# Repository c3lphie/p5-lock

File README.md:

# p5-lock

This repository contains eagle projects and libraries used in the p5 examproject

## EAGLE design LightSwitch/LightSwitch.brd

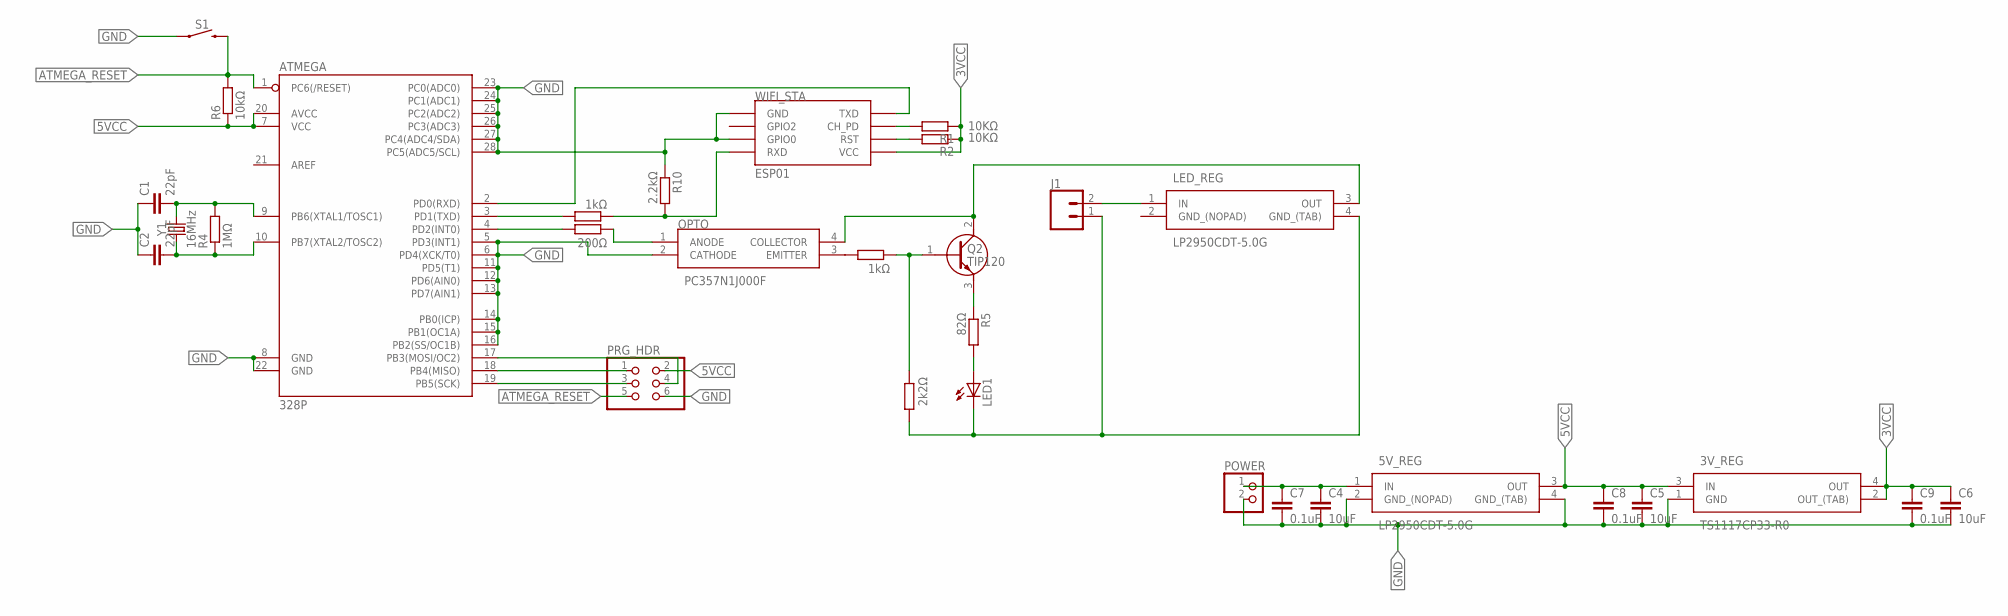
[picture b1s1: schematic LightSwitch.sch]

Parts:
3V_REG: TS1117CP33-R0; TO229P990X238-4N
5V_REG: LP2950CDT-5.0G; TO229P990X238-4N
ATMEGA: 328P; DIP28
C1, C2: 22pF; 1206
C4, C5, C6: 10uF; 1206
C7, C8, C9: 0.1uF; 1206
J1: CONN_025MM; SCREWTERMINAL-5MM-2
LED1: LED_ELD260; LED_LD260
LED_REG: LP2950CDT-5.0G; TO229P990X238-4N
OPTO: PC357N1J000F; SOP254P675X300-4N
POWER: PINHD-1X2; 1X02
PRG_HDR: PINHD-2X3; 2X03
Q2: TIP120; TO220
R1, R2: 10KΩ; R1210
R3: 200Ω; R1210
R4: 1MΩ; R1210
R5: 82Ω; R1210
R6: 10kΩ; R1210
R7, R9: 1kΩ; R1210
R8: 2k2Ω; R1210
R10: 2.2kΩ; R1210
S1: MOMENTARY-SWITCH-SPST-PTH-6.0MM; TACTILE_SWITCH_PTH_6.0MM
WIFI_STA: ESP01
Y1: 16MHz; HC49UP

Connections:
3VCC: 3V_REG.2 (OUT_(TAB)), 3V_REG.4 (OUT), C6.1, C9.1, R1.1, R2.1, WIFI_STA.VCC
5VCC: 3V_REG.3 (IN), 5V_REG.3 (OUT), ATMEGA.7 (VCC), ATMEGA.20 (AVCC), C5.1, C8.1, PRG_HDR.2, R6.1
ATMEGA_RESET: ATMEGA.1 (PC6(/RESET)), PRG_HDR.5, R6.2, S1.3 (2)
AT_TXD: ATMEGA.3 (PD1(TXD)), R9.2
GND: 3V_REG.1 (GND), 5V_REG.2 (GND_(NOPAD)), 5V_REG.4 (GND_(TAB)), ATMEGA.5 (PD3(INT1)), ATMEGA.6 (PD4(XCK/T0)), ATMEGA.8 (GND), ATMEGA.11 (PD5(T1)), ATMEGA.12 (PD6(AIN0)), ATMEGA.13 (PD7(AIN1)), ATMEGA.14 (PB0(ICP)), ATMEGA.15 (PB1(OC1A)), ATMEGA.16 (PB2(SS/OC1B)), ATMEGA.22 (GND), ATMEGA.23 (PC0(ADC0)), ATMEGA.24 (PC1(ADC1)), ATMEGA.25 (PC2(ADC2)), ATMEGA.26 (PC3(ADC3)), ATMEGA.27 (PC4(ADC4/SDA)), ATMEGA.28 (PC5(ADC5/SCL)), C1.1, C2.1, C4.2, C5.2, C6.2, C7.2, C8.2, C9.2, OPTO.2 (CATHODE), POWER.2, PRG_HDR.6, R10.1, S1.1, WIFI_STA.GND, WIFI_STA.GPIO0
GND_(NOPAD): LED_REG.2 (GND_(NOPAD))
LED_ANODE: LED1.A, R5.2
LED_EN: ATMEGA.4 (PD2(INT0)), R3.2
LED_GND: J1.1, LED1.K (C), LED_REG.4 (GND_(TAB)), R8.2
LED_VCC: LED_REG.3 (OUT), OPTO.4 (COLLECTOR), Q2.2 (C)
LED_VIN: J1.2, LED_REG.1 (IN)
MISO: ATMEGA.18 (PB4(MISO)), PRG_HDR.1
MOSI: ATMEGA.17 (PB3(MOSI/OC2)), PRG_HDR.4
unnamed: OPTO.3 (EMITTER), R7.2
unnamed: Q2.3 (E), R5.1
OPTO_ANODE: OPTO.1 (ANODE), R3.1
OPTO_EMITTER: Q2.1 (B), R7.1, R8.1
SCK: ATMEGA.19 (PB5(SCK)), PRG_HDR.3
STA_CH_PD: R1.2, WIFI_STA.CH_PD
STA_RST: R2.2, WIFI_STA.RST
STA_RXD: R9.1, R10.2, WIFI_STA.RX (RXD)
STA_TXD: ATMEGA.2 (PD0(RXD)), WIFI_STA.TX (TXD)
VIN: 5V_REG.1 (IN), C4.1, C7.1, POWER.1
XTAL1: ATMEGA.9 (PB6(XTAL1/TOSC1)), C1.2, R4.2, Y1.2
XTAL2: ATMEGA.10 (PB7(XTAL2/TOSC2)), C2.2, R4.1, Y1.1

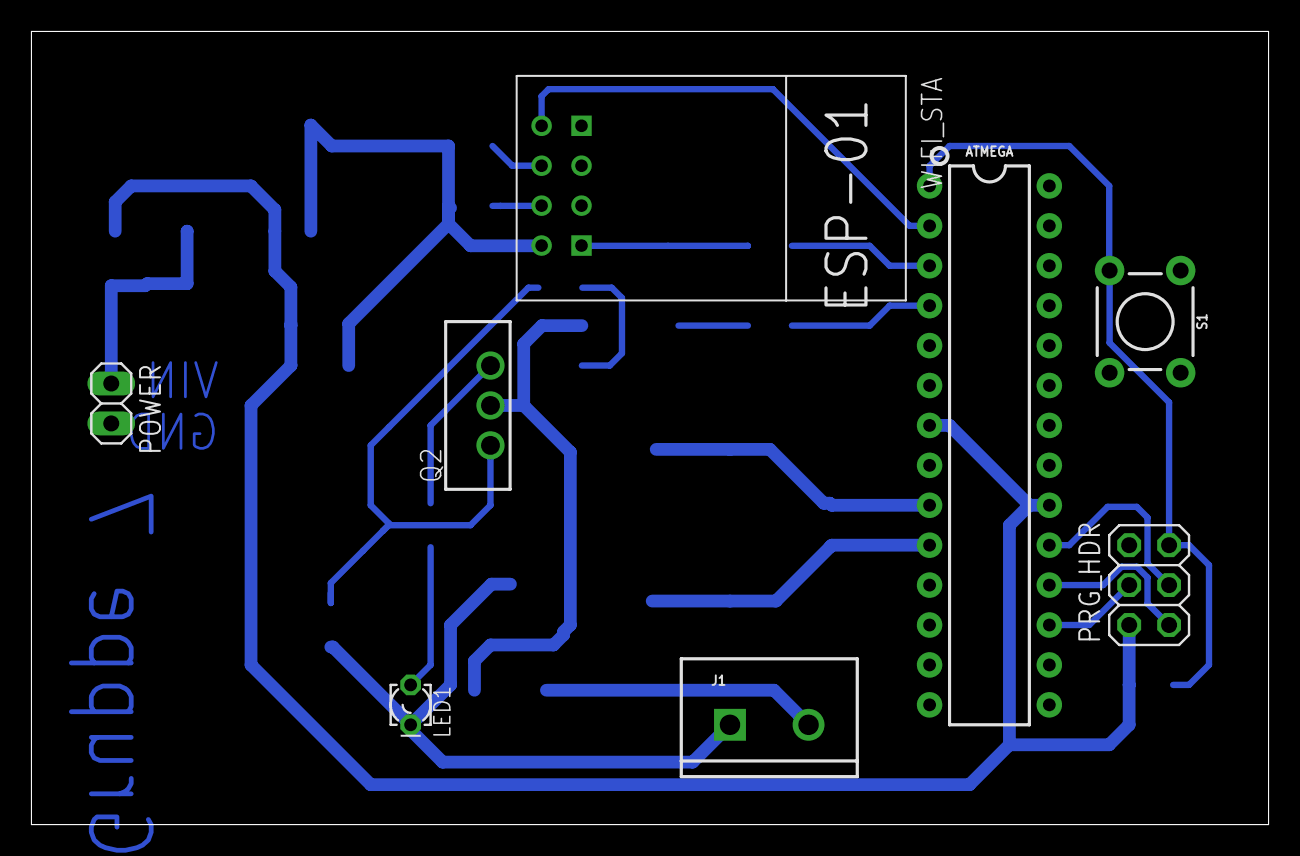
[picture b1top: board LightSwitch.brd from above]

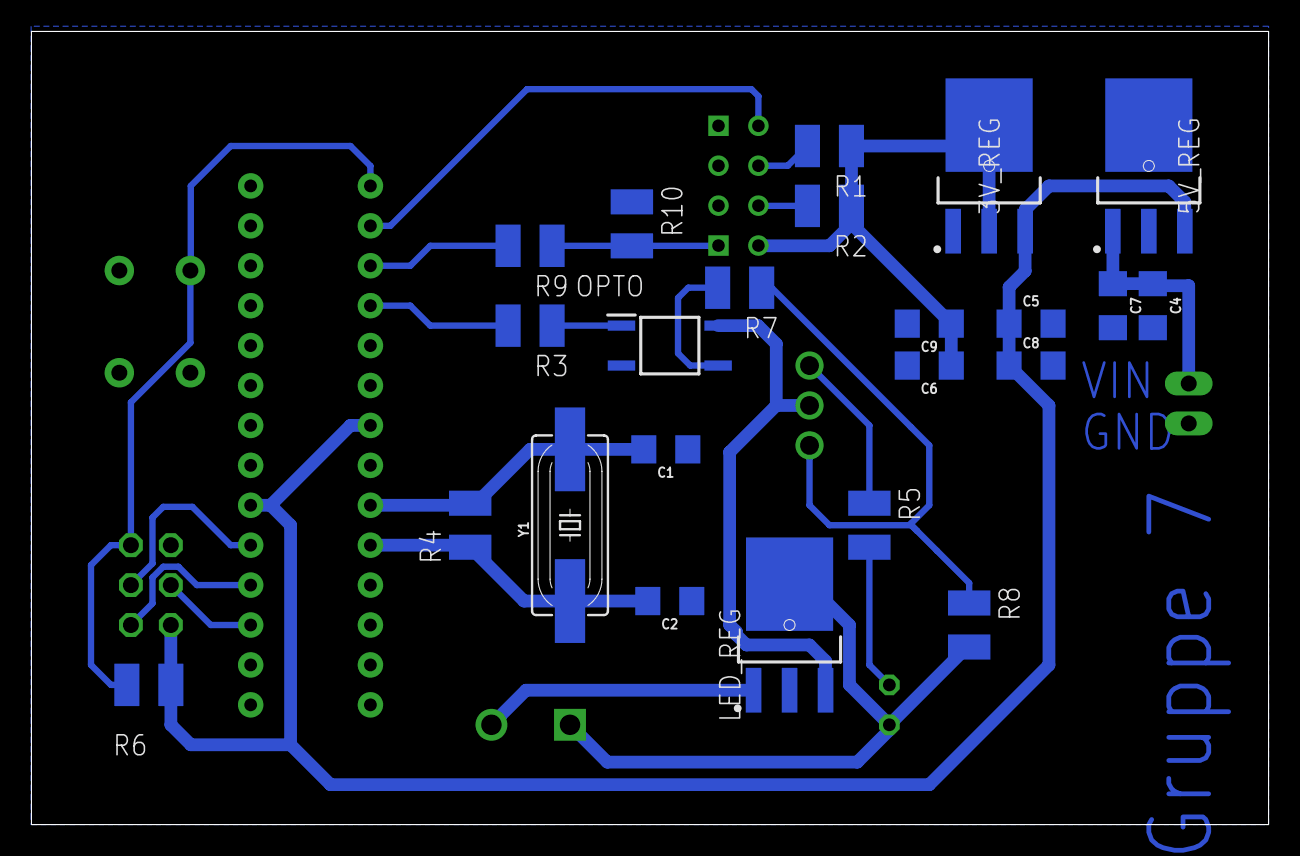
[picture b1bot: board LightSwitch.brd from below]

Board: 2 copper layers, 78.7 x 50.5 mm, 31 parts (23 on the bottom side), 24 nets.

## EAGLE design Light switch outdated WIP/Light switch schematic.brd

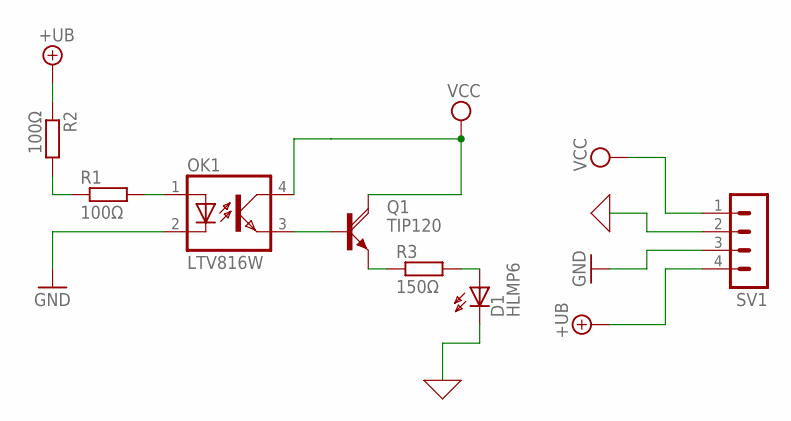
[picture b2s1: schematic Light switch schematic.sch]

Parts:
D1: HLMP6
OK1: LTV816W; DIL4-SMD
Q1: TIP120; TO220AH
R1, R2: 100Ω; 0207/10
R3: 150Ω; 0207/10
SV1: MA04-1

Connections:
0: D1.K, SV1.2
+UB: R2.1, SV1.4
GND: OK1.2 (C), SV1.3
unnamed: OK1.3 (EMIT), Q1.B
unnamed: OK1.1 (A), R1.2
unnamed: R1.1, R2.2
unnamed: Q1.E, R3.1
unnamed: D1.A, R3.2
VCC: OK1.4 (COL), Q1.C, SV1.1

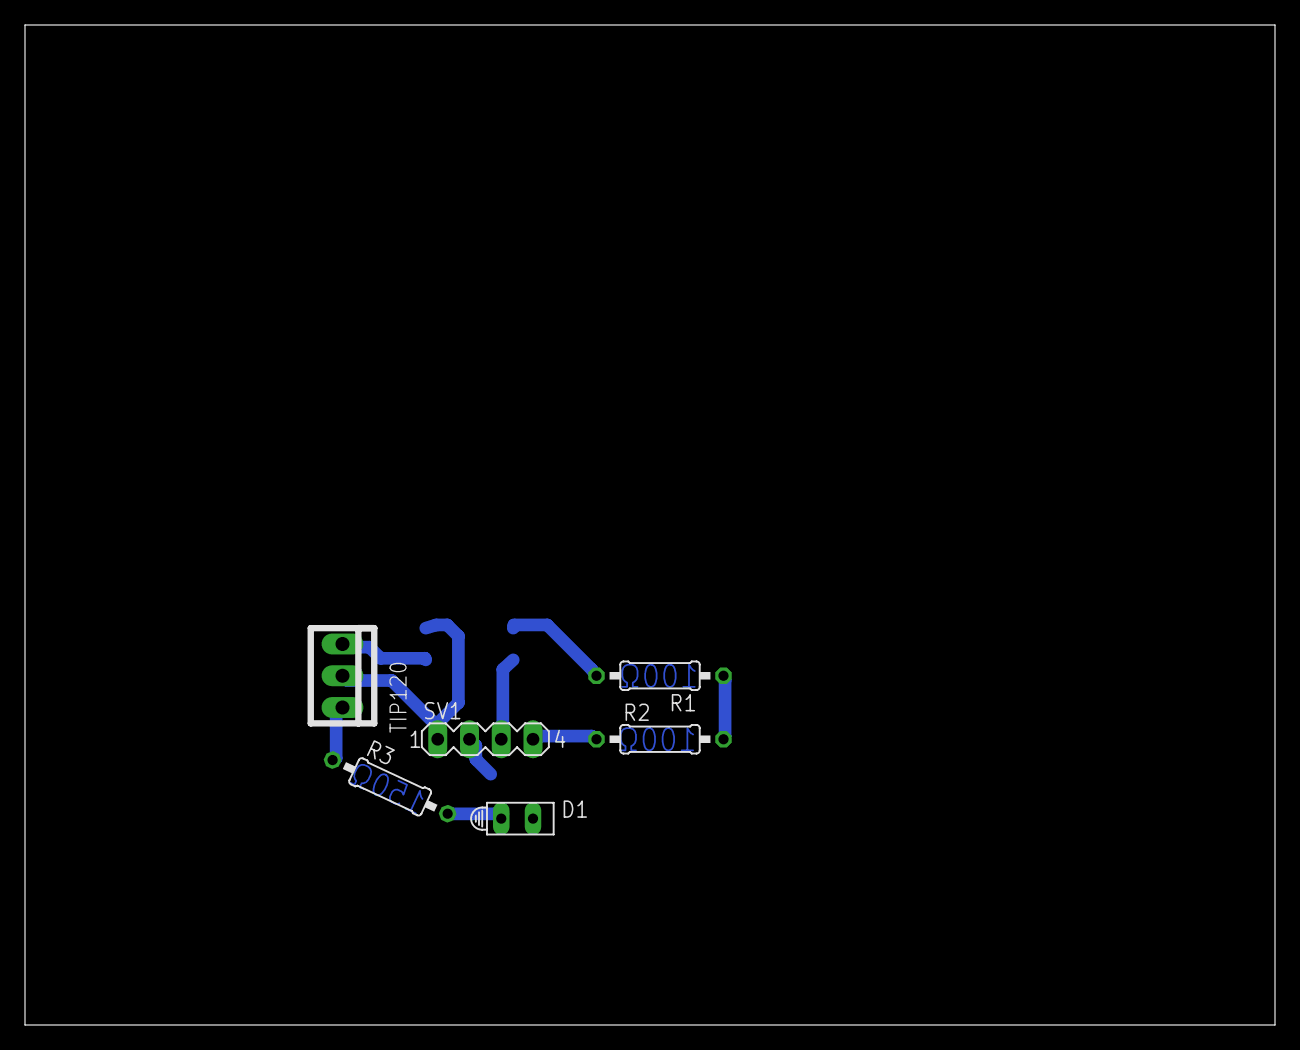
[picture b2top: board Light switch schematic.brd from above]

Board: 2 copper layers, 100.0 x 80.0 mm, 7 parts (1 on the bottom side), 9 nets.

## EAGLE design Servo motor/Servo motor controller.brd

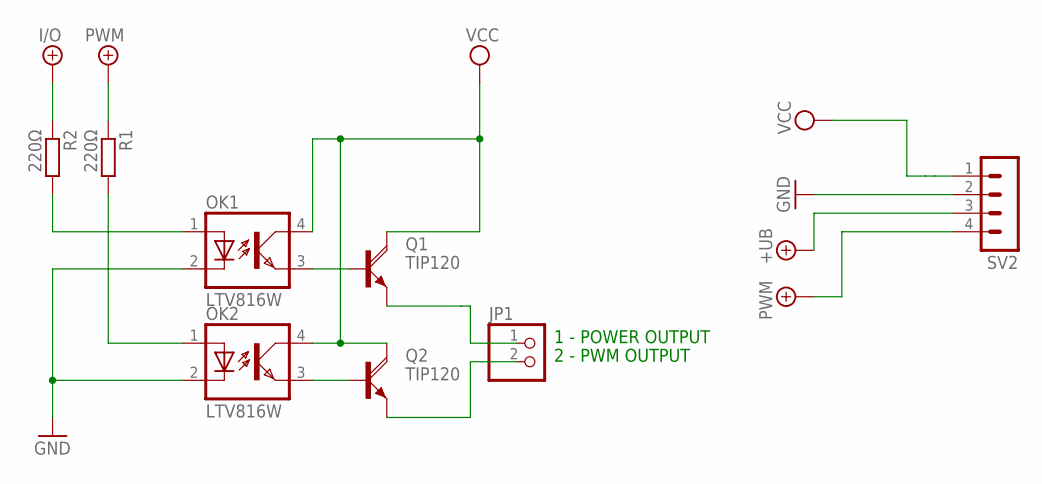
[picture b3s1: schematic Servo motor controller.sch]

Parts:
JP1: PINHD-1X2; 1X02
OK1, OK2: LTV816W; DIL4-SMD
Q1, Q2: TIP120; TO220AH
R1, R2: 220Ω; 0207/10
SV2: MA04-1

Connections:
+5V/1: R1.1, SV2.4
+UB: R2.1, SV2.3
GND: OK1.2 (C), OK2.2 (C), SV2.2
unnamed: OK1.3 (EMIT), Q1.B
unnamed: OK1.1 (A), R2.2
unnamed: OK2.1 (A), R1.2
unnamed: OK2.3 (EMIT), Q2.B
unnamed: JP1.2, Q2.E
unnamed: JP1.1, Q1.E
VCC: OK1.4 (COL), OK2.4 (COL), Q1.C, Q2.C, SV2.1

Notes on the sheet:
1 - POWER OUTPUT
2 - PWM OUTPUT

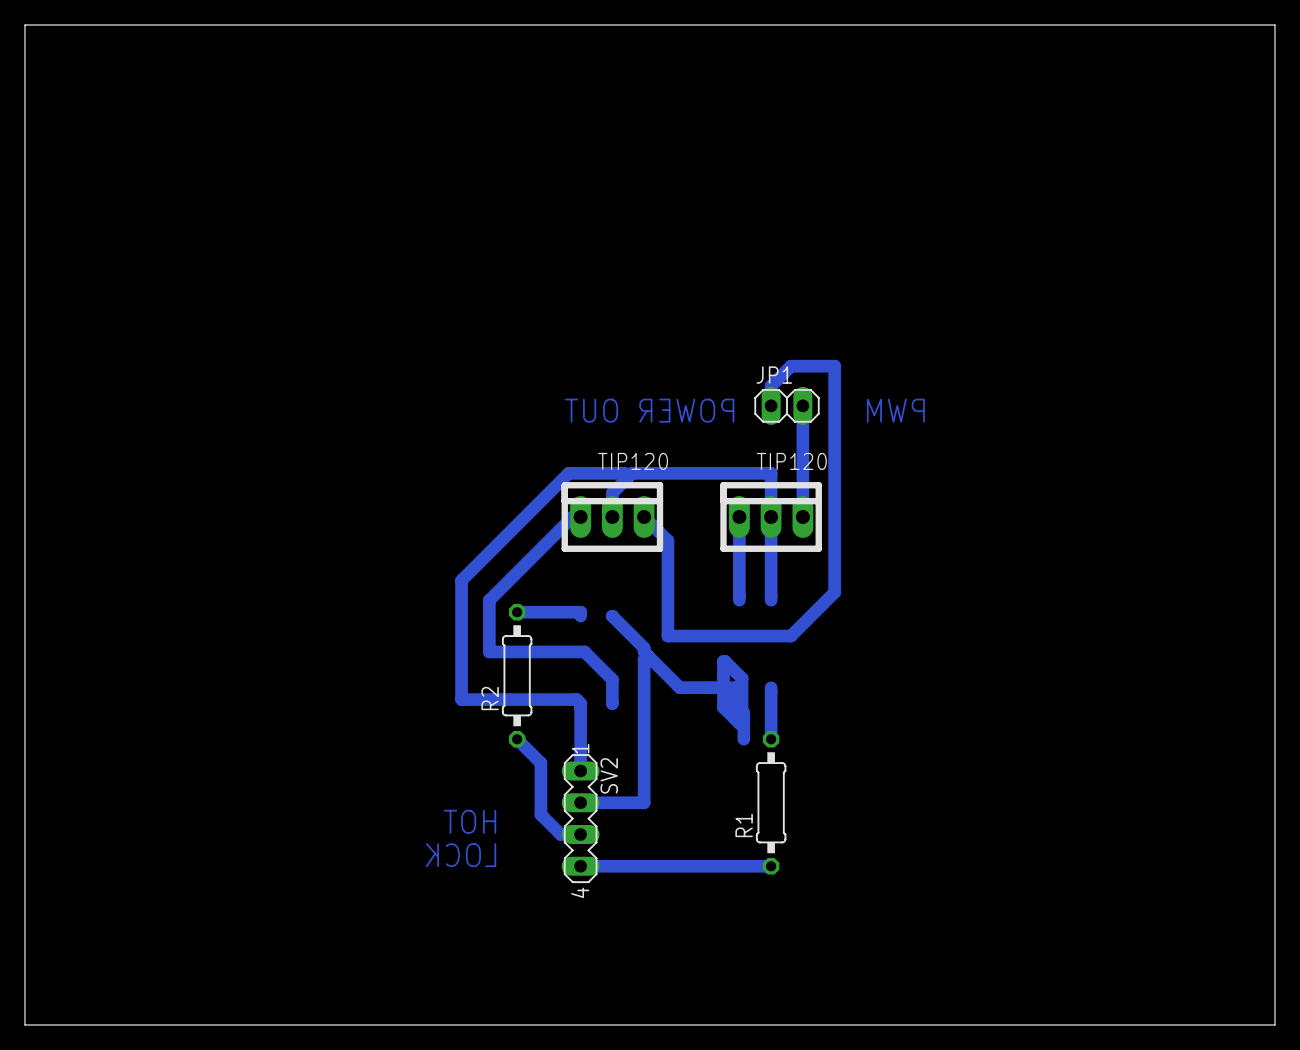
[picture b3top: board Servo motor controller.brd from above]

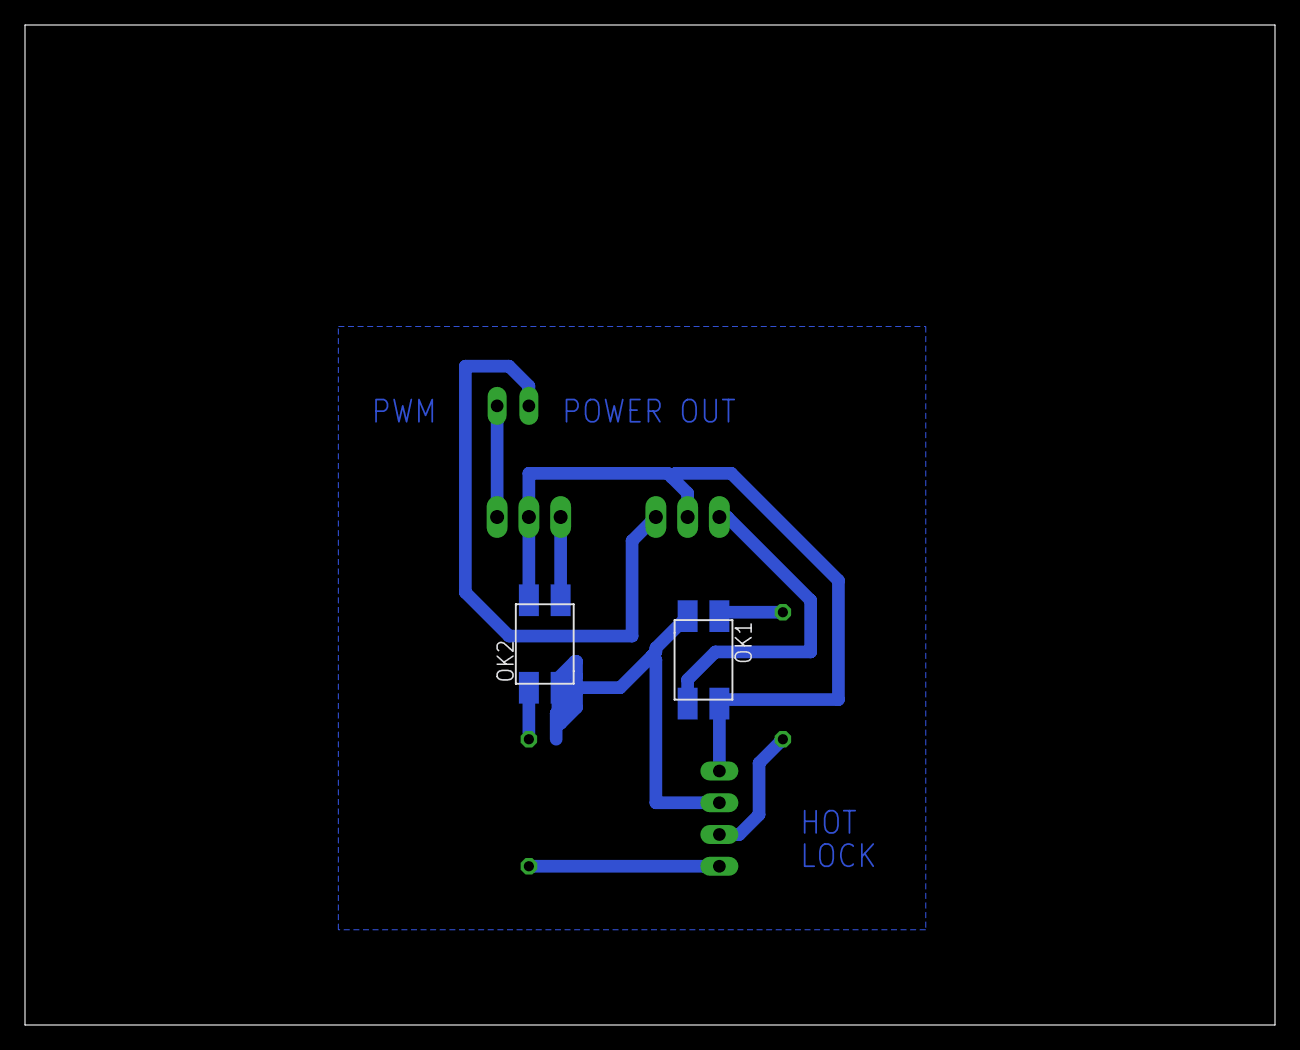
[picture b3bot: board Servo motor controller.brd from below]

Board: 2 copper layers, 100.0 x 80.0 mm, 8 parts (2 on the bottom side), 10 nets.

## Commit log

2019-03-25 Add gitignore
2019-03-25 add CAMOutput to gitignore
2019-03-25 Add README.md
2019-03-25 fix gitignore
2019-03-25 add WifiTracker and esp8266 library
2019-03-25 WifiTracker v1 schematic done
2019-03-25 Schematic done
2019-03-25 Progress
2019-03-25 Rev 1
2019-03-25 Change width on xtal
2019-03-25 Added dot
2019-03-25 Change generic voltage regulator with specific one
2019-03-25 Add power net class and added width
2019-03-25 Add power input text
2019-03-25 WifiTracker just got smaller
2019-03-29 Added 5v to 3.3V regulators to Wifitrackers
2019-03-29 Changed 3.3V regulator
2019-03-29 Remove library autosaves
2019-03-29 Prepare to print
2019-04-04 LightSwitch
2019-04-04 Rename
2019-04-04 Fix stub wire
2019-04-05 ServoMotor
2019-04-05 Edited name of outdated projects
2019-04-05 Add resistors and voltage regulator as well as pinheader
2019-04-05 Updated ServoMotor
2019-04-05 my name chef
2019-04-09 Updated Boards, mainly changing up the Servomotor print due to cluttering
2019-04-12 wifitracker fix

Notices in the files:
parts and their libraries:
SparkFun-IC-Microcontroller: Licensing: Creative Commons ShareAlike 4.0 International - https://creativecommons.org/licenses/by-sa/4.0
